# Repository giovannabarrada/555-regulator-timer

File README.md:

# 555 Timer Regulator

## Overview
This project implements a basic voltage regulation and timing circuit using the NE555 integrated circuit.

The goal is to revisit fundamental concepts of analog electronics and document the complete design process.

## Objectives
- Design a NE555-based circuit
- Create schematic and PCB
- Document design decisions and lessons learned

## Status
- In development

## Tools
- KiCad
- NE555

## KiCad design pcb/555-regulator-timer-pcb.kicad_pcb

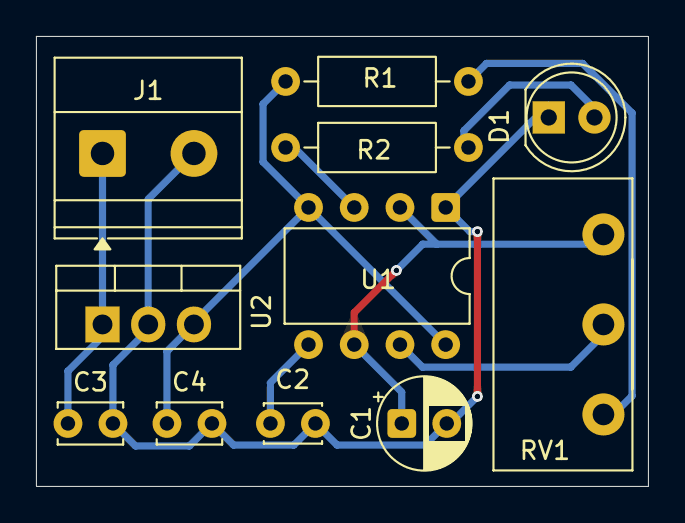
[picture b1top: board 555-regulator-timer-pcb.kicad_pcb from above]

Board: 2 copper layers, 34.0 x 25.0 mm, 11 parts (0 on the bottom side), 9 nets.

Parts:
C1: 100uF; CP_Radial_D5.0mm_P2.50mm
C2: 0.01uF; C_Disc_D3.0mm_W2.0mm_P2.50mm
C3: 0.33uF; C_Disc_D3.4mm_W2.1mm_P2.50mm
C4: 0.1uF; C_Disc_D3.4mm_W2.1mm_P2.50mm
D1: LED; LED_D5.0mm
J1: Screw_Terminal_01x02; TerminalBlock_Phoenix_MKDS-1,5-2-5.08_1x02_P5.08mm_Horizont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
R1: 1kΩ; R_Axial_DIN0207_L6.3mm_D2.5mm_P10.16mm_Horizontal
R2: 330Ω; R_Axial_DIN0207_L6.3mm_D2.5mm_P10.16mm_Horizontal
RV1: 10kΩ; potentiometer
U1: NE555P; DIP-8_W7.62mm
U2: LM7805_TO220; TO-220-3_Vertical

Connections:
+5V: C4.1, R1.2, U1.4 (R), U1.8 (VCC), U2.3 (VO)
+12V: C3.1, J1.1, U2.1 (VI)
GND: C1.2, C2.2, C3.2, C4.2, D1.1 (K), J1.2, U1.1 (GND), U2.2 (GND)
unnamed: D1.2 (A), R2.2
unnamed: R1.1, RV1.1
unnamed: C2.1, U1.5 (CV)
unnamed: RV1.2, U1.7 (DIS)
unnamed: R2.1, U1.3 (Q)
unnamed: C1.1, RV1.3, U1.2 (TR), U1.6 (THR)

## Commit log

2025-12-26 README.md
